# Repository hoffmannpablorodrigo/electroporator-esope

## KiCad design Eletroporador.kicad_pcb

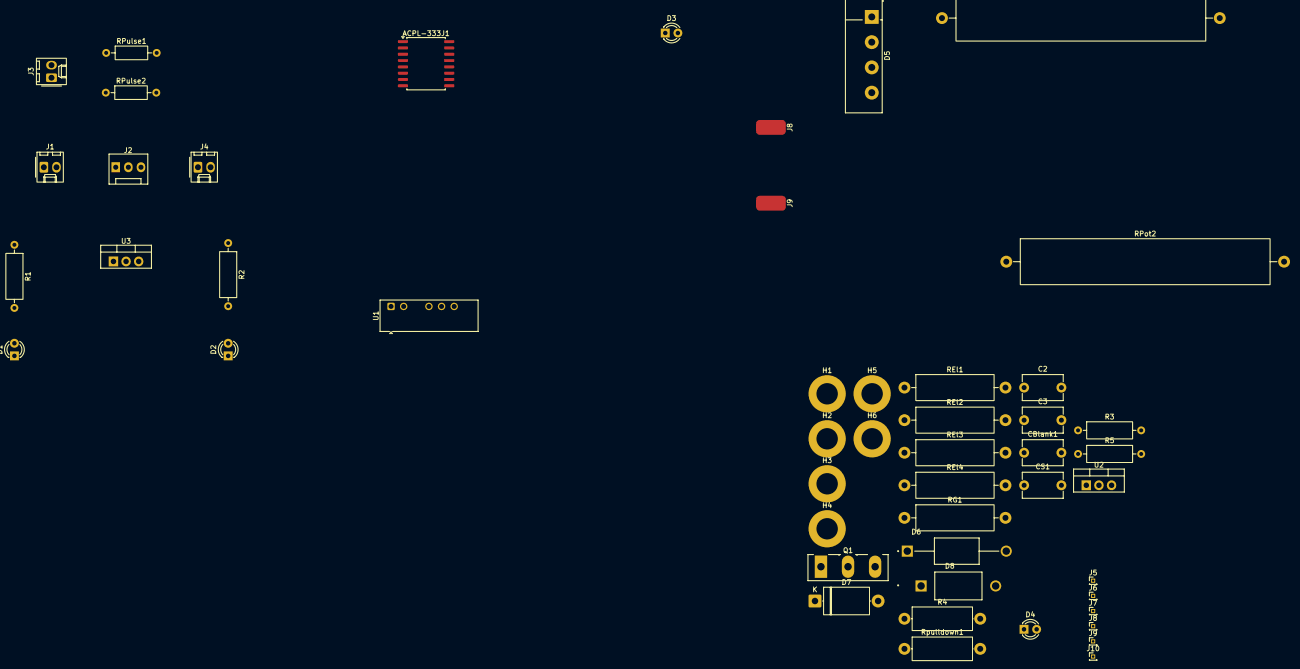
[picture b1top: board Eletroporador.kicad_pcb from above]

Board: 2 copper layers, 50 parts (0 on the bottom side), 26 nets, no tracks yet.

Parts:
ACPL-333J1: Conn_02x08_Counter_Clockwise; SOIC-16W_7.5x10.3mm_P1.27mm
C2, C3: 0.1uF; C_Disc_D8.0mm_W5.0mm_P7.50mm
CBlank1: 180pF; C_Disc_D8.0mm_W5.0mm_P7.50mm
CS1: 1nF; C_Disc_D8.0mm_W5.0mm_P7.50mm
D1, D2, D3, D4: LED; LED_D3.0mm
D5: GBU4A; Diode_Bridge_Vishay_KBU
D6: MUR460; DIOAD1990W125L900D530
D7: Ska 1/17; D_DO-201AE_P12.70mm_Horizontal
D8: MUR4100; DIOAD1950W125L950D560
H1, H2, H3, H4, H5, H6: MountingHole_Pad; MountingHole_4.3mm_M4_DIN965_Pad
J1, J3, J4: Conn_01x02; Molex_KK-254_AE-6410-02A_1x02_P2.54mm_Vertical
J2: Conn_01x03; FanPinHeader_1x03_P2.54mm_Vertical
J5, J6, J7, J8#2, J9#2, J10: Conn_01x01_Pin; PinHeader_1x01_P1.00mm_Vertical
J8, J9: Conn_01x01; SolderWirePad_1x01_SMD_3x6mm
Q1: IRG4PH50KD; TO-247-3_Vertical
R1: 1k; R_Axial_DIN0309_L9.0mm_D3.2mm_P12.70mm_Horizontal
R2: 330; R_Axial_DIN0309_L9.0mm_D3.2mm_P12.70mm_Horizontal
R3: 2.2k; R_Axial_DIN0309_L9.0mm_D3.2mm_P12.70mm_Horizontal
R4: 100; R_Axial_DIN0414_L11.9mm_D4.5mm_P15.24mm_Horizontal
R5: 1.8k; R_Axial_DIN0309_L9.0mm_D3.2mm_P12.70mm_Horizontal
REl1, REl2, REl3, REl4: 330k; R_Axial_DIN0516_L15.5mm_D5.0mm_P20.32mm_Horizontal
RG1: 10; R_Axial_DIN0516_L15.5mm_D5.0mm_P20.32mm_Horizontal
RPot1: 10; R_Axial_Power_L50.0mm_W9.0mm_P55.88mm
RPot2: 47; R_Axial_Power_L50.0mm_W9.0mm_P55.88mm
RPulse1, RPulse2: 180; R_Axial_DIN0207_L6.3mm_D2.5mm_P10.16mm_Horizontal
Rpulldown1: 47k; R_Axial_DIN0414_L11.9mm_D4.5mm_P15.24mm_Horizontal
U1: TMA-0512D; Converter_DCDC_TRACO_TMA-05xxD_12xxD_Dual_THT
U2: LM7818_TO220; TO-220-3_Vertical
U3: LM7805_TO220; TO-220-3_Vertical

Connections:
+12V: J1.2, J2.2, J5.1 (Pin_1_1), R1.1, U3.1 (VI)
/5V: J4.2, J7.1 (Pin_1_1), R2.1, U1.1 (+Vin), U3.3 (VO)
/12V_PWR: J8#2.1 (Pin_1_1), R3.1, U1.6 (+Vout), U2.1 (VI)
/15,5V_gate1: ACPL-333J1.11, RG1.2, Rpulldown1.1
/15,5V_gate2: ACPL-333J1.10, Q1.1 (G), RG1.1
/18V: ACPL-333J1.13, C2.2, C3.1, J9#2.1 (Pin_1_1), R5.1, U2.3 (VO)
/Ctrl_pulsos: J3.2, RPulse1.1
/HV0F: D5.2, H2.1 (1_1)
/HV0N: D5.3, H1.1 (1_1)
/HV1A: D5.1 (+), RPot1.1
/HV1B: D6.C, D7.1 (A1), H3.1 (1_1), H5.1 (1_1), REl1.2, RPot1.2
/HV2B: REl1.1, REl2.2
/HV3B: REl2.1, REl3.2
/HV4B: REl3.1, REl4.2
/HV5B_Source: D8.A, H6.1 (1_1), Q1.2 (C), REl4.1, RPot2.1
/HV6B: CS1.1, D8.C, RPot2.2
GND: D1.1 (K), D2.1 (K), J1.1, J2.1, J3.1, J4.1, J6.1 (Pin_1_1), RPulse2.1, U1.2 (-Vin), U3.2 (GND)
GNDPWR: ACPL-333J1.9, ACPL-333J1.12, ACPL-333J1.16, C2.1, C3.2, CBlank1.1, CS1.2, D3.1 (K), D4.1 (K), D5.4 (-), D7.2 (A2), H4.1 (1_1), J10.1 (Pin_1_1), Q1.3 (E), Rpulldown1.2, U1.4 (-Vout), U2.2 (GND)
unnamed: ACPL-333J1.5, ACPL-333J1.8, RPulse2.2
unnamed: ACPL-333J1.6, ACPL-333J1.7, RPulse1.2
unnamed: ACPL-333J1.14, CBlank1.2, R4.1
unnamed: D1.2 (A), R1.2
unnamed: D2.2 (A), R2.2
unnamed: D3.2 (A), R3.2
unnamed: D4.2 (A), R5.2
unnamed: D6.A, R4.2
